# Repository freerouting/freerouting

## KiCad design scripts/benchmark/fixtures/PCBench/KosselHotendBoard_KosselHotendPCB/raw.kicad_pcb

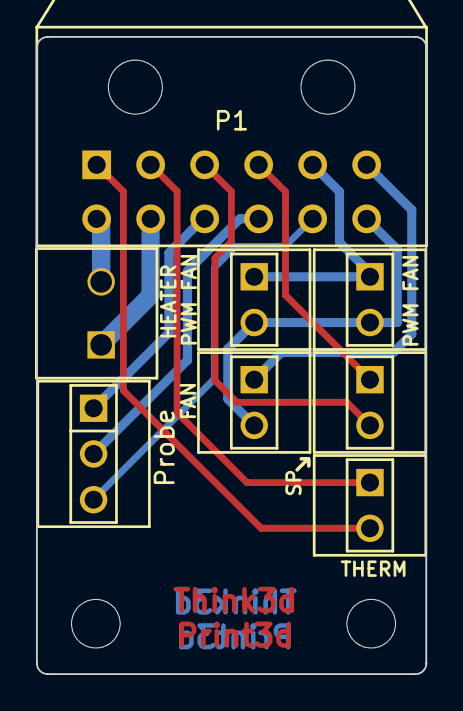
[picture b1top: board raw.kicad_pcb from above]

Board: 2 copper layers, 21.6 x 35.4 mm, 8 parts (0 on the bottom side), 12 nets.

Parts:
P1: CONN_6X2; PIN_ARRAY_6x2_lugs
P2: HEATER; 3.5MM_2X1
P3: THERM; PIN_ARRAY_2X1_KK
P4, P7: PWM FAN; PIN_ARRAY_2X1_KK
P5: FAN; PIN_ARRAY_2X1_KK
P6: Probe; PIN_ARRAY_3X1_KK
P8: SP; PIN_ARRAY_2X1_KK

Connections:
+12V: P1.2, P2.2
FAN +: P1.12, P4.2, P5.2, P7.2
GND: P1.11, P5.1
Heater -VE: P1.4, P2.1
PWM Fan -VE: P1.9, P4.1, P7.1
Probe GND: P1.8, P6.2
Probe Sig: P1.10, P6.3
Spare1: P1.7, P8.1
Spare2: P1.5, P8.2
Therm1: P1.3, P3.1
Therm2: P1.1, P3.2
Vcc: P1.6, P6.1

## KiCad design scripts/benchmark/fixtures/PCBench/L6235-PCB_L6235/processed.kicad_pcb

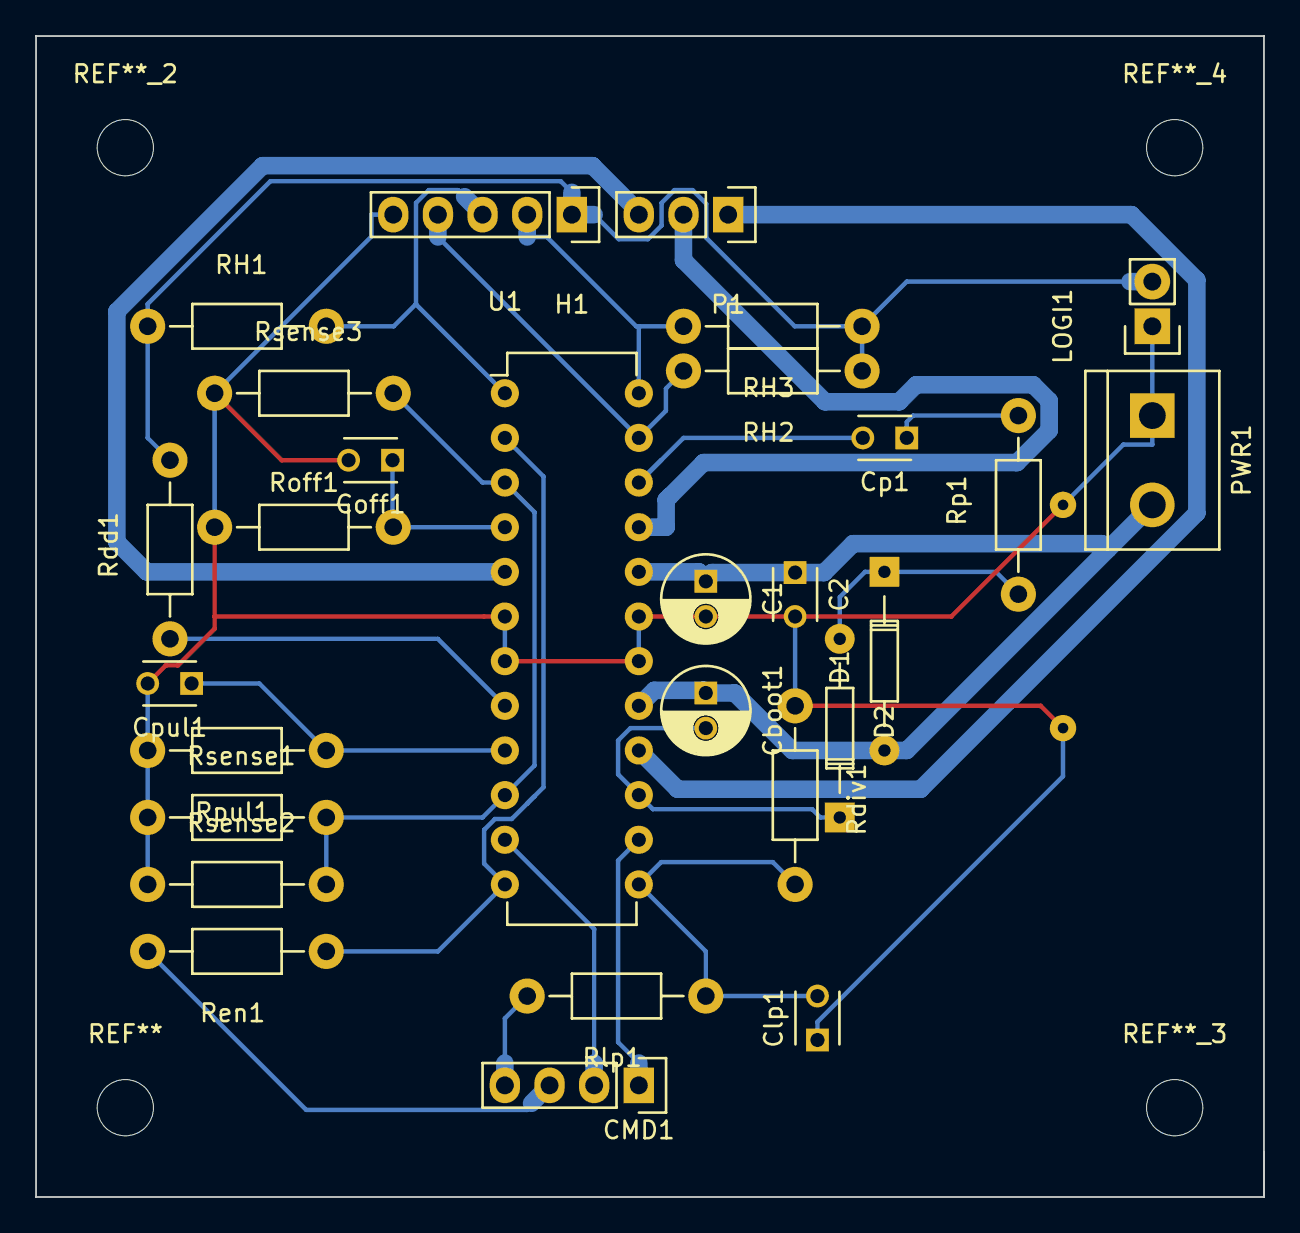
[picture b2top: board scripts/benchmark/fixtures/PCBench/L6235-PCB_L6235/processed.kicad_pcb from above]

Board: 2 copper layers, 69.8 x 66.0 mm, 30 parts (0 on the bottom side), 23 nets.

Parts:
C1: 10µ; C_Radial_D5_L11_P2
C2: 100n; C_Disc_D3_P2.5
CMD1: CONN_01X04; Socket_Strip_Straight_1x04
Cboot1: 220n; C_Radial_D5_L11_P2
Clp1: 100n; C_Disc_D3_P2.5
Coff1: 1n; C_Disc_D3_P2.5
Cp1: 10n; C_Disc_D3_P2.5
Cpul1: 10n; C_Disc_D3_P2.5
D1, D2: 1N4148; Diode_DO-35_SOD27_Horizontal_RM10
H1: CONN_01X05; Socket_Strip_Straight_1x05
LOGI1: CONN_01X02; Socket_Strip_Straight_1x02
Noname_1, Noname_2: pad_gnd
P1: CONN_01X03; Socket_Strip_Straight_1x03
PWR1: CONN_01X02; bornier2
RH1, RH2, RH3: 10K; Resistor_Horizontal_RM10mm
Rdd1: 1k; Resistor_Horizontal_RM10mm
Rdiv1: 15k; Resistor_Horizontal_RM10mm
Ren1: 100k; Resistor_Horizontal_RM10mm
Rlp1: 56k; Resistor_Horizontal_RM10mm
Roff1: 33k; Resistor_Horizontal_RM10mm
Rp1: 100; Resistor_Horizontal_RM10mm
Rpul1: 47k; Resistor_Horizontal_RM10mm
Rsense1, Rsense2, Rsense3: 1; Resistor_Horizontal_RM10mm
U1: L6235N; DIP-24_W7.62mm

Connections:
+5V: H1.1, LOGI1.2, RH1.1, RH2.1, RH3.1, Rdd1.2
/BRAKE: CMD1.1, U1.14
/ENABLE: CMD1.3, Ren1.2
/FWD/REV: CMD1.2, U1.11
/HALL1: H1.3, RH1.2, U1.1
/HALL2: H1.4, RH2.2, U1.23
/HALL3: H1.2, RH3.2, U1.24
/PHASE1: P1.3, U1.5
/PHASE2: P1.2, U1.21
/PHASE3: P1.1, U1.16
/VREF: CMD1.4, Rlp1.2
GND: C1.2, C2.2, Clp1.1, Coff1.2, Cpul1.2, H1.5, LOGI1.1, Noname_1.1, Noname_2.1, PWR1.1, Rdiv1.1, Roff1.2, Rpul1.2, Rsense1.1, Rsense2.1, Rsense3.1, U1.6, U1.7, U1.18, U1.19
unnamed: Cboot1.2, D2.1, U1.15
unnamed: Clp1.2, Rdiv1.2, Rlp1.1, U1.13
unnamed: Coff1.1, Roff1.1, U1.4
unnamed: Cp1.1, Rp1.2
unnamed: Cp1.2, U1.22
unnamed: Cpul1.1, Rpul1.1, U1.9
unnamed: D1.1, D2.2, Rp1.1
unnamed: Rdd1.1, U1.8
unnamed: Ren1.1, U1.2, U1.12
unnamed: Rsense1.2, Rsense2.2, Rsense3.2, U1.3, U1.10
VSS: C1.1, C2.1, Cboot1.1, D1.2, PWR1.2, U1.17, U1.20

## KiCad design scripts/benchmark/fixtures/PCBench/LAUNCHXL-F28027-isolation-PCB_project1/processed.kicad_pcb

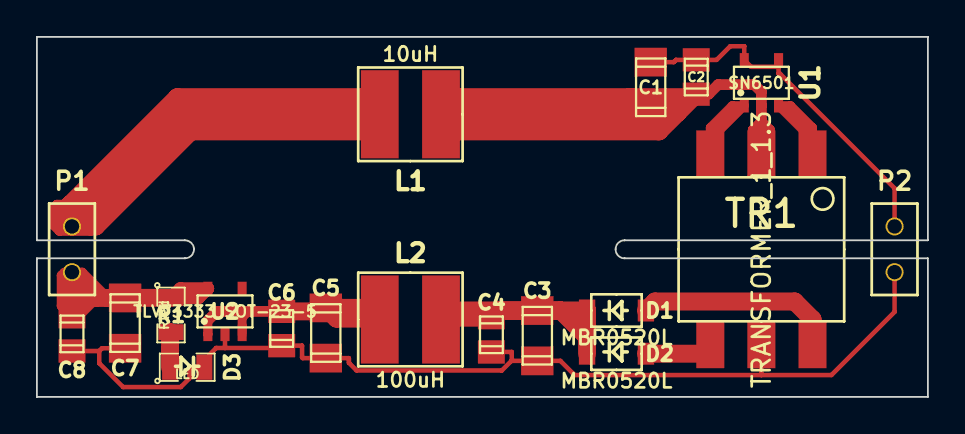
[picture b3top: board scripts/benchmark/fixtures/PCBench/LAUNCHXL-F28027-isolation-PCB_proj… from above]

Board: 2 copper layers, 49.5 x 20.0 mm, 19 parts (0 on the bottom side), 12 nets.

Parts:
C1, C3, C5, C7: 4.7u; c_1206
C2, C4, C6, C8: 100n; c_0805
D1, D2: MBR0520L; SOD-123
D3: LED; SM0805
L1: 10uH; VLCF5020
L2: 100uH; VLCF5020
P1, P2: CONN_2; PIN_ARRAY_2X1
R1: Rled; SM0805
TR1: TRANSFORMER_1_1.3; transf_isol_wurth
U1: SN6501; SOT23-5
U2: TLV73333 SOT-23-5; SOT23-5

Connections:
3.3V: L1.1, P1.2
3.3V isol: C7.1, C8.1, P1.1, R1.1, U2.5
GND: C1.2, C2.2, P2.2, U1.4, U1.5
GND_isol: C3.2, C4.2, C5.2, C6.2, C7.2, C8.2, D3.2, P2.1, TR1.5, U2.2
unnamed: C1.1, C2.1, L1.2, TR1.2, U1.2
unnamed: D3.1, R1.2
unnamed: TR1.1, U1.3
unnamed: TR1.3, U1.1
unnamed: C3.1, C4.1, D1.2, D2.2, L2.1
unnamed: D1.1, TR1.6
unnamed: D2.1, TR1.4
unnamed: C5.1, C6.1, L2.2, U2.1, U2.3

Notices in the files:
scripts/benchmark/fixtures/PCBench/KosselHotendBoard_KosselHotendPCB/raw.kicad_pcb:
(c) Licensed under the CERN OHL V1.2
CERN OHL 1.2
